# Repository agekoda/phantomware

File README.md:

<div align="center">

  <h1> phantomware </h1>
  <p> Compact, powerful ESP32-S3 platform for IR, NFC, sensors, WiFi & more. </p>

<!-- Badges -->

<h4>

</h4>
</div>

## 🔥 Overview

Phantomware is a fully custom-built multi-tool device based on the ESP32-S3, designed for wireless analysis, signal interaction, and hardware experimentation.

It combines RF, GPIO, IR, and NFC capabilities into a portable platform featuring a 240×320 TFT display, SD card storage, and a 3000mAh battery system with a full charging circuit, MAX17055 fuel gauge, and built-in overcharge and overcurrent protection.

With 6 navigation buttons and a modular software framework, Phantomware is built for advanced IoT development, prototyping, and hardware exploration.

<div align="center"> 
  
</div>

<div>&nbsp;</div>

## Phantomware vs. Flipper Zero

| Feature | Phantomware | Flipper Zero |
|--------|------------|----------------|
| Microcontroller | ESP32-S3 Dual-core Xtensa LX7 | STM32WB55RG |
| Bluetooth and WiFi? | Bluetooth 5 & WiFi 4 | Bluetooth 5.4 |
| Display | 2" 240x320 TFT LCD | 1.4" 128x64 Monochrome |
| IR Transceiver | 3x VSMY14940 LEDs + TSOP75348WTR | 3x VSMY14940 + TSOP75338TR |
| NFC Support | PN532 via SPI | ST25R3916 |
| Battery & Power Mgmt | 3000mAh LiPo + TP4056 + MAX17055 | 2100mAh + BQ25896 + BQ27220 |
| Expansion Options | Micro SD + 16 GPIOs | Micro SD + 18 GPIOs |
| Target Use Case | Signal analysis, RFID/NFC, IR, tinkering | Sub-GHz, RFID/NFC, IR, utility |
| Open Source? | Open Source & fully customisable | Open Source with limitations |
| Typical Price Point | ~$50 USD | ~$200 USD |

> [!NOTE]
> Information for Flipper Zero is based on publicly available specifications and may vary.

## 🚀 Features

### 🔌 GPIO Toolkit

* PWM signal generator
* Oscilloscope
* Frequency analyser
* Voltmeter
* Resistor calculator
* USB to UART bridge

### 📡 WiFi Tools *(educational use only)*

* Network scan
* Packet monitor
* Spectrum waterfall
* Deauthentication Attack
* Beacon spam
* Evil portal / Captive portal
* Access point hosting
* Connect to AP and host HTML

### 📶 Bluetooth Tools

* BLE scanning
* Device advertisement spam (Apple / Samsung / Windows)

### ⌨️ HID Tools

* BadUSB
* BadBT (Bluetooth HID attacks)

### 💬 Communication

* ESP-NOW messaging
* NRF24-based chat system

### 🧩 Expansion Support

* GPS modules
* PN532 NFC module
* Future GPIO-based add-ons

<!-- nRFBOX V2 -->
## 📸 Versions

<table>
  <tr>
    <td style="text-align: center;">
      
      <p style="font-style: italic; font-size: 14px; margin-top: 5px;">v1 prototype based on ESP32</p>
    </td>    
    <td style="text-align: center;">
      
      <p style="font-style: italic; font-size: 14px; margin-top: 5px;">v2 based on ESP32-S3</p>
    </td>
    </td>    
    <td style="text-align: center;">
      
      <p style="font-style: italic; font-size: 14px; margin-top: 5px;">v3 based on ESP32-S3 with PCBA and battery</p>
    </td>
  </tr>
</table>

## 🚨 Disclaimer

This project is intended for **educational and research purposes only**.

Do not use this device to interfere with networks, devices, or signals that you do not own or have explicit permission to test. Misuse may violate local laws and regulations.

<!-- License -->
## ⚠️ License

Distributed under the MIT License. See LICENSE.txt for more information.

<!-- Contact -->
## 🤝 Contact

Email - hello@designedbykoda.com

Project Link: [https://github.com/agekoda/phantomware](https://github.com/agekoda/phantomware)

<div>&nbsp;</div>

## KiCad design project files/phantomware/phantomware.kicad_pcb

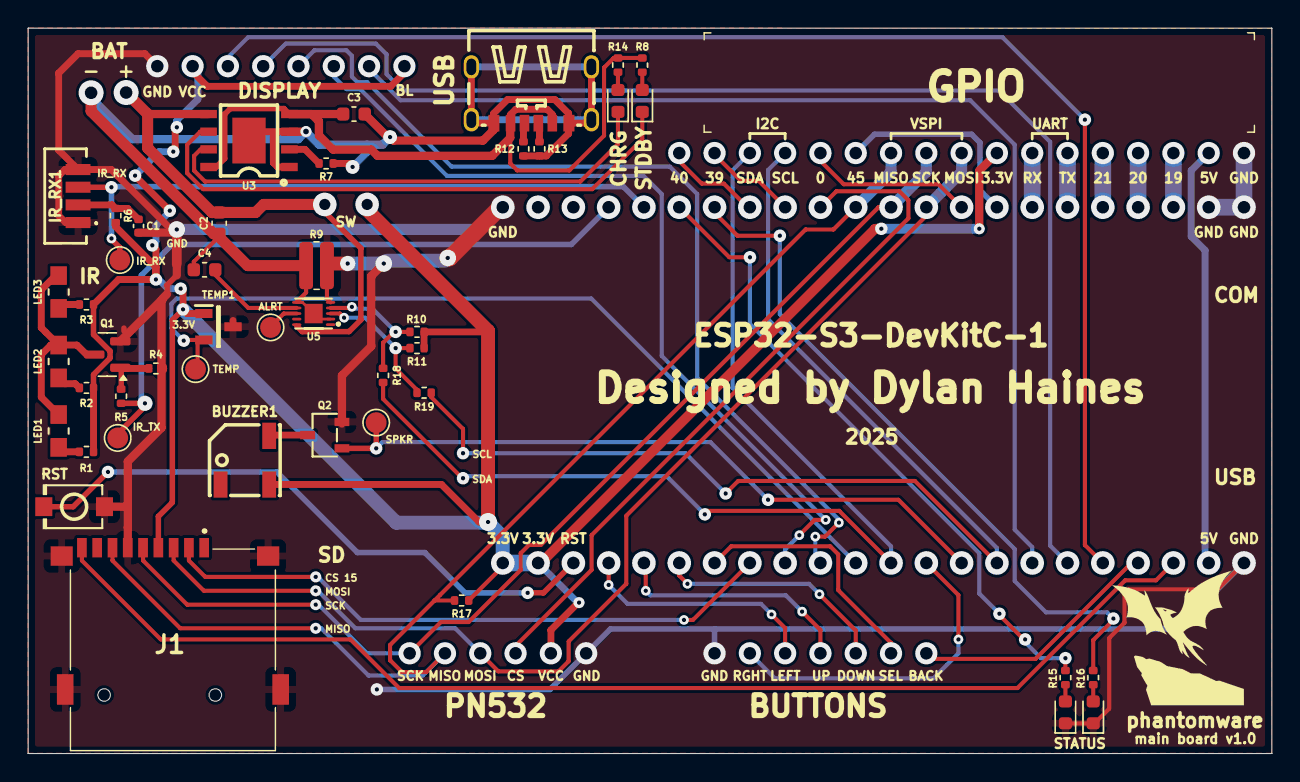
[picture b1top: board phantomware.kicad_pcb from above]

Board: 2 copper layers, 89.5 x 52.2 mm, 45 parts (0 on the bottom side), 28 nets.

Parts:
ALRT: TestPoint_Pad_D1.5mm
ALRT#2: TestPoint_Pad_D1.5mm
BUZZER1: 4kHz; smd5x5
C1: 100nF; C_0402_1005Metric
C2, C3: 10 uF; C_0603_1608Metric
C4: 0.47 uF; C_0603_1608Metric
CHRG: RED; LED_0603_1608Metric
IR_RX1: TSOP75338TR
J1: TF-15X15; TF15X15
LED1, LED2, LED3: VSMY14940
LED4: GREEN; LED_0603_1608Metric
LED5: RED; LED_0603_1608Metric
Q1: DMN2058U; SOT-23
Q2: L2N7002KLT1G
R1, R2, R3: 39; R_0402_1005Metric
R4, R17: 10k; R_0402_1005Metric
R5: 130; R_0402_1005Metric
R6: 10; R_0402_1005Metric
R7: 1.1k; R_0402_1005Metric
R8, R15, R18, R19: 1k; R_0402_1005Metric
R9: 10m; R_0612_1632Metric
R10, R11: 4.7k; R_0402_1005Metric
R12, R13: 5.1k; R_0402_1005Metric
R14, R16: 560; R_0402_1005Metric
RST: TS-1088-AR02016
STDBY: GREEN; LED_0603_1608Metric
TEMP: TestPoint_Pad_D1.5mm
TEMP1: MCP9701AT-E_TT; SOT95P237X112-3N
TEMP#2, TEMP#3: TestPoint_Pad_D1.5mm
U3: TP4056
U5: MAX17055ETB+
USB1: TYPE-C-SMD_TYPE-C-6P_5

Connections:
+3.3V: BUZZER1.1, C1.1, IR_RX1.2 (VS), J1.4 (VDD), R1.1, R2.1, R3.1, R6.1, R6.2, R10.1, R11.1, R17.1, TEMP1.1 (VDD)
GND: C1.2, IR_RX1.1 (GND), IR_RX1.4 (GND), J1.6 (VSS), J1.MP1, J1.MP2, J1.MP3, J1.MP4, LED4.1 (K), LED5.1 (K), Q1.2 (S), Q2.2 (S), R4.2, R9.2, RST.1, TEMP1.3 (GND), U5.5 (CSN)
IO41: LED5.2 (A), R16.1, R16.2
IO42: LED4.2 (A), R15.1, R15.2
unnamed: C2.1, U3.5 (BAT), U5.10 (BATT)
unnamed: C2.2, C3.2, C4.1, R7.2, R9.1, R12.1, R13.2, U3.1 (TEMP), U3.3 (GND), U3.9 (EP), U5.2 (AIN), U5.6 (CSP), U5.11 (EP), USB1.7 (EH), USB1.A12 (GND), USB1.B12 (GND)
unnamed: IR_RX1.3 (OUT), TEMP#3.1
unnamed: J1.7 (DAT0), R17.2
unnamed: LED1.1, R1.2
unnamed: LED3.1, R3.2
unnamed: LED2.1, R2.2
unnamed: CHRG.2 (A), R14.1
unnamed: CHRG.1 (K), U3.7 (CHRG#)
unnamed: R8.2, STDBY.2 (A)
unnamed: STDBY.1 (K), U3.6 (STDBY#)
unnamed: LED1.2, LED2.2, LED3.2, Q1.3 (D)
unnamed: Q1.1 (G), R4.1, R5.2
unnamed: BUZZER1.2, Q2.3 (D)
unnamed: ALRT.1, Q2.1 (G)
unnamed: TEMP1.2 (VOUT), TEMP#2.1
unnamed: R5.1, TEMP.1
unnamed: C3.1, R8.1, R14.2, U3.4 (VCC), U3.8 (CE), USB1.A9 (VBUS), USB1.B9 (VBUS)
unnamed: R7.1, U3.2 (PROG)
unnamed: C4.2, U5.7 (REG)
unnamed: R11.2, R19.1, R19.2, U5.3 (SCL)
unnamed: R10.2, R18.1, R18.2, U5.4 (SDA)
unnamed: R13.1, USB1.A5 (CC1)
unnamed: R12.2, USB1.B5 (CC2)

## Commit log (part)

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2025-06-22 Change .jpg to .png
2025-06-23 Create test
2025-07-13 replace front and back.png
2026-03-07 Add pcb image
2026-04-27 Upload logo
2026-04-27 Rename to koda.png
2026-04-27 Initialize README with project details and features
    Added detailed project description, features, and comparison with Flipper Zero.
2026-04-27 Rename Gemini_Generated_Image_8iau6i8iau6i8iau.png to kodalogo
2026-04-27 Rename kodalogo to kodalogo.png

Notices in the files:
project files/phantomware/phantomware.kicad_pcb:
© dylan haines 2025
